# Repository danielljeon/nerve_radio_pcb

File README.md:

# nerve_radio_pcb

Radio and power supply module
to [`nerve_pcb`](https://github.com/danielljeon/nerve_pcb).

---

<details markdown="1">
  <summary>Table of Contents</summary>

<!-- TOC -->
* [nerve_radio_pcb](#nerve_radio_pcb)
  * [1 Overview](#1-overview)
  * [2 Board Specifications](#2-board-specifications)
    * [2.1 Connectors](#21-connectors)
    * [2.2 Switching Buck Regulator](#22-switching-buck-regulator)
  * [3 Release Notes](#3-release-notes)
    * [3.1 v0.1.0-alpha](#31-v010-alpha)
    * [3.2 v1.0.0 (WIP)](#32-v100-wip)
<!-- TOC -->

</details>

---

## 1 Overview

|                           Top                            |                             Bottom                             |                     v0.1.0-alpha                     |
|:--------------------------------------------------------:|:--------------------------------------------------------------:|:----------------------------------------------------:|
|  |  |  |

---

## 2 Board Specifications

### 2.1 Connectors

Connectors fixed by hardware (PCB traces or the connector itself).

| Connector                       | Ref | Description                                                                  |
|---------------------------------|:---:|------------------------------------------------------------------------------|
| LMR51430 buck (5 V) regulator   | J1  | Pin 1: Ground, Pin 2: VIN supply (> 5 V, <= 36 V)                            |
| Bottom side 2x10 board-to-board | J2  | See schematic/layout for details                                             |
| 5 V GPIO/PWM breakout           | J3  | Pin 1: 5 V, Pin 2-3: GPIO/PWM 1-2 (5 V), Pin 5: Ground                       |
| SPI breakout                    | J4  | Pin 1: 3.3 V, Pin 2: MISO, Pin 3: MOSI, Pin 4: CLK, Pin 5: CS, Pin 6: Ground |

### 2.2 Switching Buck Regulator

The `LMR51430` is used for the 5 V (3 A) supply from a 4.5 V to 36 V input.

Also chosen based on previous experience and testing from a previous
project, [robotic_hand_pcb](https://github.com/danielljeon/robotic_hand_pcb).
See documentation
at [robotic_hand_pcb/blob/main/README.md#5-switching-buck-regulator](https://github.com/danielljeon/robotic_hand_pcb/blob/main/README.md#5-switching-buck-regulator).

---

## 3 Release Notes

### 3.1 v0.1.0-alpha

- Pre-release 4-layer board variant.
    - Short-term pre-release board bring-up/testing release.
- Order date: 2025/01/13.

### 3.2 v1.0.0 (WIP)

- Incremented major version since `v0.1.0-alpha` pre-release due to partial
  redesign including full component changes.
    - Buck converter redesign (TPSM843x20 -> LMR51430), reasoning:
        - Potential supply chain risks and cost.
        - Improved compatibility in common buck converter IC footprints.
        - Reduced restrictions on space allocated for power supply circuits.
        - Improved input voltage range (> 5 V, <= 36 V) -> (> 5 V, <= 17 V).
        - Easier to test due to exposed switch node.

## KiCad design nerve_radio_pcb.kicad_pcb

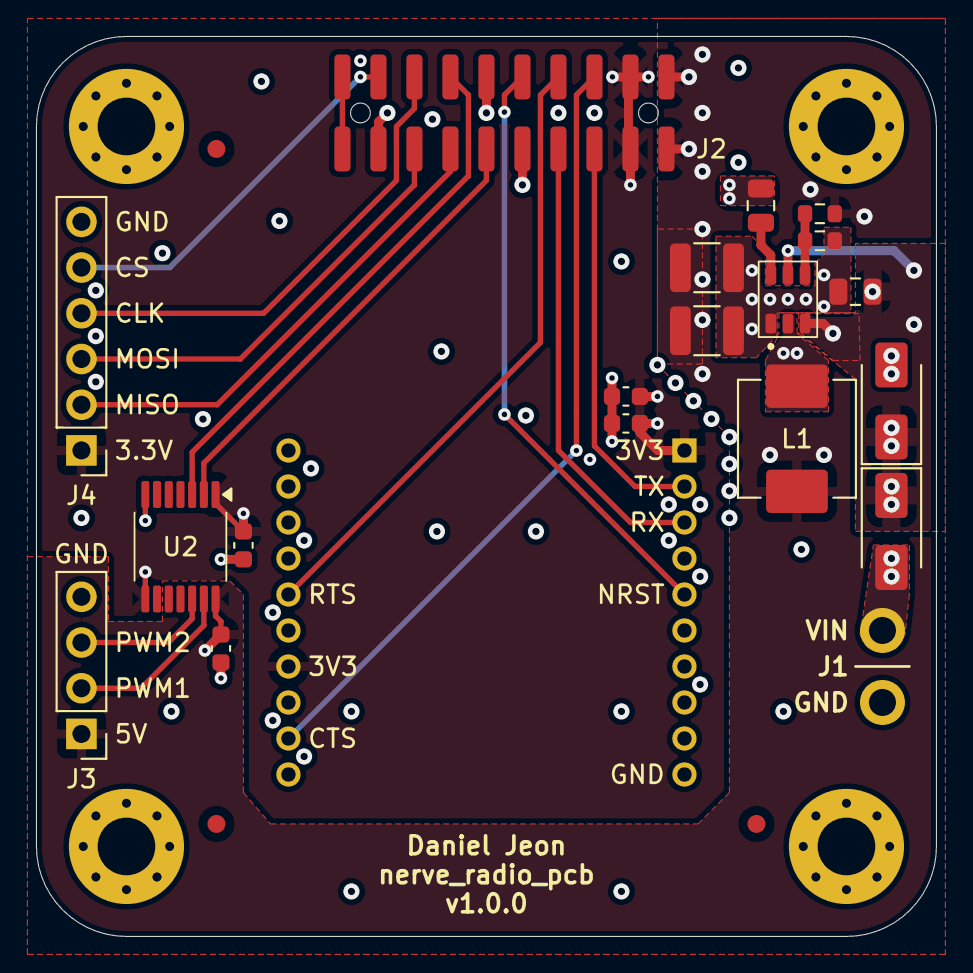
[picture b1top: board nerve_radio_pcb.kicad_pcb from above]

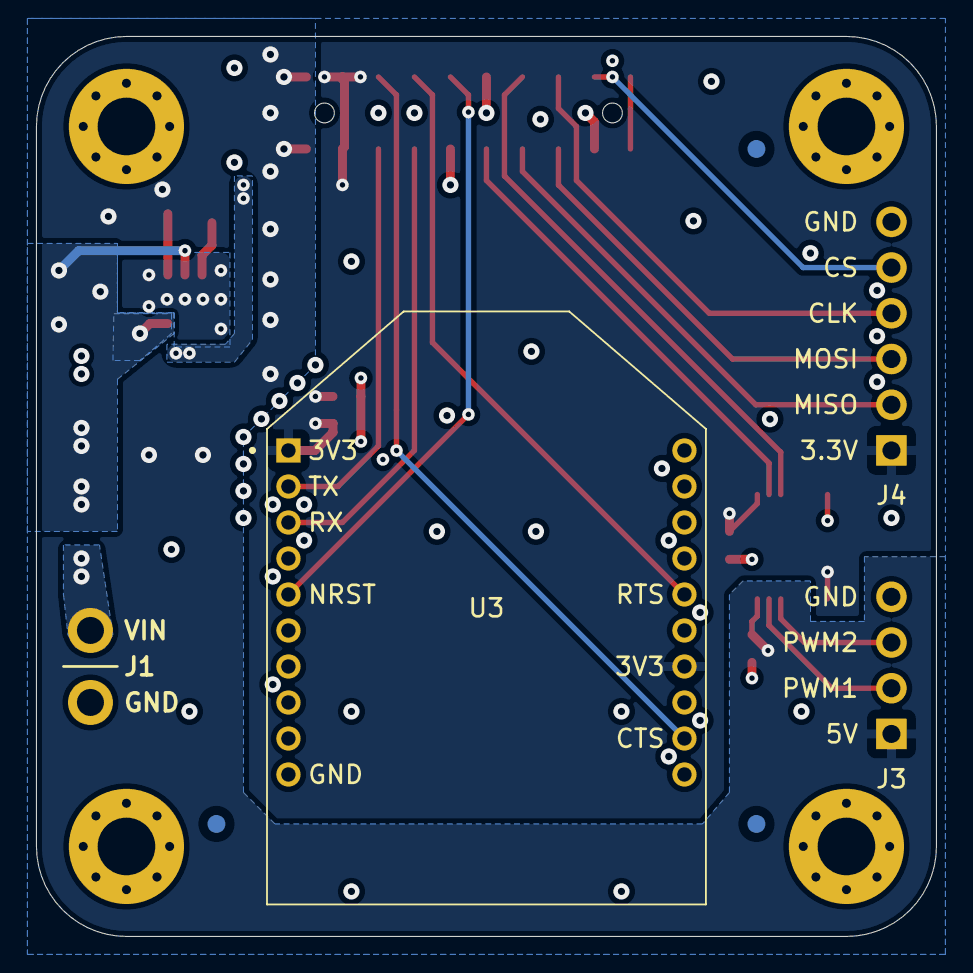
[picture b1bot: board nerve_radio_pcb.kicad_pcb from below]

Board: 4 copper layers, 50.0 x 50.0 mm, 30 parts (4 on the bottom side), 22 nets.

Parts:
C1: 100n; C_0805_2012Metric
C2, C3: 100n; C_0603_1608Metric
C4: 2u2; C_0805_2012Metric
C5, C6: 22u; C_1210_3225Metric
C7: 47p; C_0603_1608Metric
C8: 1u; C_0603_1608Metric
D1: SK36A-LTP; D_SMA
D2: SMAJ15A-13-F; D_SMA
FM1, FM2, FM3, FM4, FM5, FM6: 1mm; Fiducial_1mm_Mask2mm
H1, H2, H3, H4: M3; MountingHole_3.2mm_M3_Pad_Via
J1: Battery; battery
J2: BF030-20A-B1-0360-0277-0600-LB; bf030-20a-b1-0360-0277-0600-lb
J3: 5V GPIO Breakout; PinHeader_1x04_P2.54mm_Vertical
J4: 3V SPI Breakout; PinHeader_1x06_P2.54mm_Vertical
L1: 6u8; vishay_ihlp-2525cz
R1: 100k; R_0603_1608Metric
R2: 13k7; R_0603_1608Metric
U1: LMR51430; lmr51430
U2: TXB0104QPWRQ1; txb0104qpwrq1
U3: XBP9B-DMWT-002; xbee_pro_900hp

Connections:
+3V3: C2.1, C7.1, C8.1, J2.3, J2.4, J4.1, U2.1 (V_{CCA}), U2.8 (OE), U3.1 (VCC), U3.14 (VREF)
+5V: C3.1, C5.2, C6.2, J2.1, J2.2, J3.1, L1.2, R1.2, U2.14 (V_{CCB})
+VSUPPLY: C4.1, D1.1 (K), D2.1 (A1), U1.3 (VIN), U1.5 (EN)
/BUCK_SW: C1.2, L1.1, U1.2 (SW)
/GPIO_1/PWM_1: J2.11, U2.2 (A1)
/GPIO_1/PWM_1_{5V}: J3.2, U2.13 (B1)
/GPIO_2/PWM_2_{5V}: J3.3, U2.12 (B2)
/GPIO_2/PWM_2/ADC_DRDY: J2.14, U2.3 (A2)
/RADIO_NRST: J2.10, U3.5 (~RESET)
/RADIO_UART_CTS: J2.6, U3.12 (~CTS/DIO7)
/RADIO_UART_RTS: J2.8, U3.16 (~RTS/DIO6)
/RADIO_UART_RX: J2.7, U3.3 (DIN/~CONFIG/DIO14)
/RADIO_UART_TX: J2.5, U3.2 (DOUT/DIO13)
/SPI_CLK: J2.16, J4.4
/SPI_CS: J2.18, J4.5
/SPI_MISO: J2.13, J4.2
/SPI_MOSI: J2.15, J4.3
GND: C2.2, C3.2, C4.2, C5.1, C6.1, C7.2, C8.2, D2.2 (A2), H1.1, H2.1, H3.1, H4.1, J1.2, J2.9, J2.12, J2.17, J3.4, J4.6, R2.2, U1.1 (GND), U2.7 (GND), U3.10 (GND)
unnamed: D1.2 (A), J1.1
unnamed: J2.19, J2.20
unnamed: C1.1, U1.6 (CB)
unnamed: R1.1, R2.1, U1.4 (FB)

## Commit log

2024-11-17 Add git and GitHub related files
2024-11-17 Add component_library submodule
2024-11-17 Add KiBot workflow
2024-11-17 Add WIP KiCad files
2024-11-17 Fix board-to-board connector pinout
2024-11-17 Move PCB dimensions to User Comments layer
2024-11-17 Pass DRC (ERC previously passed)
2024-11-18 Add KiBot badge in README.md
2024-11-19 Combine KiBot BoM directory
2024-11-19 Add stackup PCB notes
2024-11-19 Update KiBot PCB PDF gen
2024-11-20 Add ground stitching vias and silkscreen cleanup
2024-11-22 Update component_library
2024-11-26 Widen 5V rail
2024-12-03 Add initial README.md and PCB pictures
2024-12-03 Update KiBot workflow
2024-12-03 Fix KiBot workflow
2024-12-08 Cleanup revision and docs pictures
2024-12-13 Cleanup and update board-to-board connector
2024-12-13 Add missing connectors library record
2024-12-13 Regenerate PCB
2025-01-03 Update config.kibot.yaml, cleanup, add fiducials
2025-01-07 Update component_library and add 5V buck
2025-01-08 Cleanup and add missing transfer vias
2025-01-08 Remove unused via pads
2025-01-09 Major cleanup
2025-01-11 Cleanup and add battery connector
2025-01-13 Cleanup silkscreen
2025-01-14 Update docs for release
2025-01-14 Add MIT LICENSE file
2025-01-16 Update component recommendation notes
2025-01-16 Remove bad specific part suggestion notes
2025-03-08 Redesign layout for WIP v0.1.0
2025-03-08 Shorten board-to-board connector
2025-03-08 Fix previous bad commit 14902c5
2025-03-25 Update buck converter for v1.0.0 dev
    - Update component library
    - Change buck regulator design to LMR51430
    - Cleanup PCB
    - Update version info
2025-04-03 Update for KiCad 9.0 and component library
2025-04-03 Update KiBot workflow for v2_k9
2025-04-12 Update docs for LMR51430 buck
2025-04-21 Move UART RX/TX flip to board-to-board connector
2025-04-24 Standardize README.md
2025-04-28 Add minor decoupling caps and TVS/Schottky diodes
2025-04-29 Improve current path vias
2025-05-14 Update README.md for PCB module reference
2025-05-14 Add TVS and schottky diode info
2025-05-27 Cleanup and fix outer layer non-functional pads
2025-06-03 Update config.kibot.yaml for KiCad/Bot 9
2025-10-18 Add board picture
